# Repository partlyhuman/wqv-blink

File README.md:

# WQV Blink
#### A Casio WQV Series USB Sync Dongle

This is an easy-to-use, self-contained device that retrieves photos from the series of extremely cool 2000-era [Casio WQV camera watches](https://www.casio.com/us/watches/50th/Heritage/2000s/) and stores them as a USB drive.

## Manual

See the [wiki](https://github.com/partlyhuman/wqv-blink/wiki) for all instructions!

## Purchase

Pre-assembled devices ars available in limited quantities on my [Ko-Fi shop](https://ko-fi.com/s/76fb4d3271)!

## Compatibility

Firmware [wqv12](firmware/wqv12):
* WQV-1 ✅
* WQV-2 ✅

Firmware [wqv310](firmware/wqv310):
* WQV-3 ✅
* WQV-10 ✅

## Building

The PCB, case, and firmware in this repository go together as pictured here. 

Gerbers are [included](pcb/WQV1-S3-SuperMini/production/). Fabricate with basic options, nothing fancy. 1.6mm thickness, HASL is just fine.

| Reference | Value | Details |
|----|----|----|
| R1 | 0-20R | 0805 Resistor |
| C1 | 1uF | 0805 Capacitor |
| C2 | 1uF | 0805 Capacitor |
| C3 | 0.1uF | 0805 Capacitor |
| U1 | ESP32-S3 Super Micro | https://www.aliexpress.com/item/1005007523988592.html |
| U2 | SSD1306_OLED_128x64 | https://www.aliexpress.com/item/1005006141235306.html (Yellow Blue) |
| U3 | TFDU4101-TR3 | https://www.digikey.com/short/nrdh27mb |

R1 is used to save power to the IR LED. The TFDU4101 has built-in LED resistors so this can be 0R for maximum TX power. There is a lot of good info on sample circuits and component values in the [TFDU4101 datasheet (PDF)](https://www.vishay.com/docs/81288/tfdu4101.pdf)

The [case](case/) is split into a top and bottom print. It can be printed with very basic settings. With the correct orientation, no supports are needed.

Builds are made with PlatformIO. In the firmware's directory, run `pio run -e esp32_s3_supermini` or use the PlatformIO VSCode extension. Note that this will not give you the dual-boot/dual-firmware option; for this, extra scripts are included. Alternatively, if you do not need to change anything, you can use the [web updater](https://wqv.partlyhuman.com/) to program the ESP32.

## DIY Build options

Breakouts are included to make a hand-wired device possible using breadboards, perfboards, jumpers, etc.

Currently this builds on ESP32-S2 and -S3 based boards. You can choose to include a common 0.96" monochrome SSD1306 screen or not based on the Platform.io environment.

Other ESP32 SoCs like the C3 lack the hardware to support USB Device mode, which we use to mount as a USB drive. See the [Espressif USB peripheral FAQ](https://docs.espressif.com/projects/esp-faq/en/latest/software-framework/peripherals/usb.html).

PSRAM is used if found on your board, but is not required. Flash space large enough to store 99 images (<1MB) as well as the program is required, should not be an issue.

A [Vishay TFDU4101](https://www.vishay.com/en/product/81288/) is the only required external component, used for bidirectional IRDA communication with the watch. It is still in production and widely available for cheap! In this repository you will find breakout PCBs that will give it 2.54mm standard header pins, [one barebones](pcb/TFDU4101-breakout/), and a more [user-friendly one](pcb/TFDU4101-breakout-simplified/) which includes the passive components, and a solder bridge to optionally power the IR LED & logic from a single supply (recommended, up to +6V is acceptable according to the datasheet). The silkscreen gives two possible orientations of the TFDU4101 so you can choose to aim it upwards or outwards. Double-check pin 1 to make sure your orientation is correct.

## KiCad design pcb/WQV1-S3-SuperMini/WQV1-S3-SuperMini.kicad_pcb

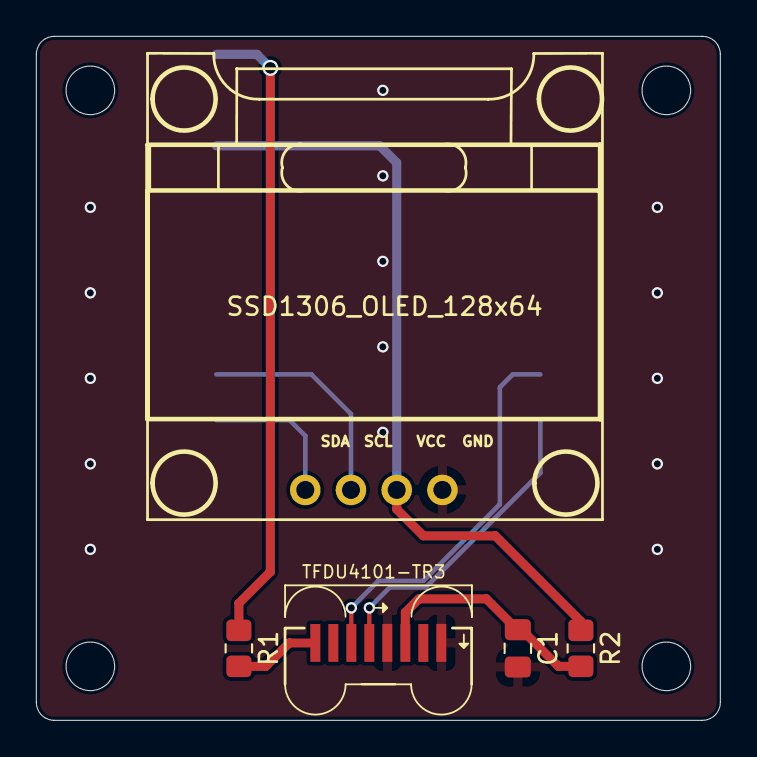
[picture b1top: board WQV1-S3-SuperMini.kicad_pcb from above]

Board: 2 copper layers, 38.0 x 38.0 mm, 10 parts (1 on the bottom side), 9 nets.

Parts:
C1: 4.7u; C_0805_2012Metric_Pad1.18x1.45mm_HandSolder
H1, H2, H3, H4: MountingHole; MountingHole_2.7mm_M2.5
R1: 0R; R_0805_2012Metric_Pad1.20x1.40mm_HandSolder
R2: 47R; R_0805_2012Metric_Pad1.20x1.40mm_HandSolder
U1: ESP32-S3 Supermini; ESP32-S3-SuperMicro_SMD
U2: SSD1306_OLED_128x64; SSD1306
U3: TFDU4101-TR3; TFDU4101 Positioning Guides

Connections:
/+3.3V: R2.1, U1.16 (3V3), U2.2 (VCC)
/+5V: R1.1, U1.18 (5V)
/GND: C1.2, U1.17 (GND), U2.1 (GND), U3.5 (SD), U3.8 (GND)
/IRDA_RX: U1.9 (GP7), U3.4 (RXD)
/IRDA_TX: U1.8 (GP6), U3.3 (TXD)
/SCL: U1.11 (GP9), U2.3 (SCL)
/SDA: U1.10 (GP8), U2.4 (SDA)
unnamed: R1.2, U3.1 (IREDANODE)
unnamed: C1.1, R2.2, U3.6 (VCC1)

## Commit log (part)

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2026-01-31 Docs!
2026-02-01 Find TFDU4101 model, fix origin in freecad, export model of breakout
2026-02-01 Make PSRAM optional again
2026-02-07 All hacks now built-in, no user intervention
2026-02-07 Inverted status bar gfx
2026-02-07 Add basic RGBLED, sanitize lib imports
2026-02-09 Larger flash partition, blink disk icon
2026-02-09 Minor tweaks
2026-02-23 Add C3 supermini for rough placement
2026-02-23 3d printed case
2026-02-24 Add BOM
2026-02-24 Restore larger screw posts
2026-03-01 Fix MSC not using same LED pin, leaving light on
2026-03-15 Rename firmware
2026-03-15 Create USB dongle mode
2026-03-15 Working irda serial device
2026-04-09 Fix Windows error on dismount by not rebooting when done, new file naming scheme
2026-04-17 Add label to drive!
2026-04-19 Trivial
2026-04-28 Stops before RCMD
2026-04-28 Getting as far as file?
2026-04-29 Better understanding of chunk header, using header info to determine no more chunks in file
2026-04-30 Use PSRAM to avoid writing two files to flash, and speed up final copy
2026-04-30 Yet again change PSRAM to just heap, sizes are perfectly manageable
2026-05-02 Better progress for 3/10
2026-05-02 Cosmetic changes
2026-05-02 Could this be all that's needed??!
2026-05-02 Move more app logic into App ns
2026-05-03 Production flashing
2026-05-04 General cleanups
2026-05-09 Add image
2026-05-16 Reorganize so jpeg core can be tested
2026-05-16 Test fixture init
2026-05-16 Fix trim end function
2026-05-16 Deleting casio metadata
2026-05-16 Looks like EXIF writing is okay
2026-05-16 Fix implementation bug with MicroExif
2026-05-16 Replacing EXIF in place so it doesn't go before JFIF
2026-05-17 Version up the web updater
2026-05-17 Minor cleanups
